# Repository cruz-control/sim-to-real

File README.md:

# Sim-to-real Team

Notes: (4/17/24) 

Solutions:
Got Jetson.GPIO to import by copying into the code directory
Got voltage out on controll pin (jetson servo PWM test)

Issues:
Get Jetson.GPIO to import from default download
Get the servo to run

Links:

Gave us test code
https://forums.developer.nvidia.com/t/strange-behaviour-with-jetson-nano-devkit-pwm-signal/113004/2

Gave us secondary test code
https://stackoverflow.com/questions/69114674/enabling-and-working-with-jetson-gpio-pins-with-python

Possible solution to Jetson.GPIO importing into python
https://forums.developer.nvidia.com/t/jetson-gpio-is-installed-but-cannot-be-imported/264719

Other possible help for identifying PWM and using PWM
https://kernel.org/doc/Documentation/pwm.txt

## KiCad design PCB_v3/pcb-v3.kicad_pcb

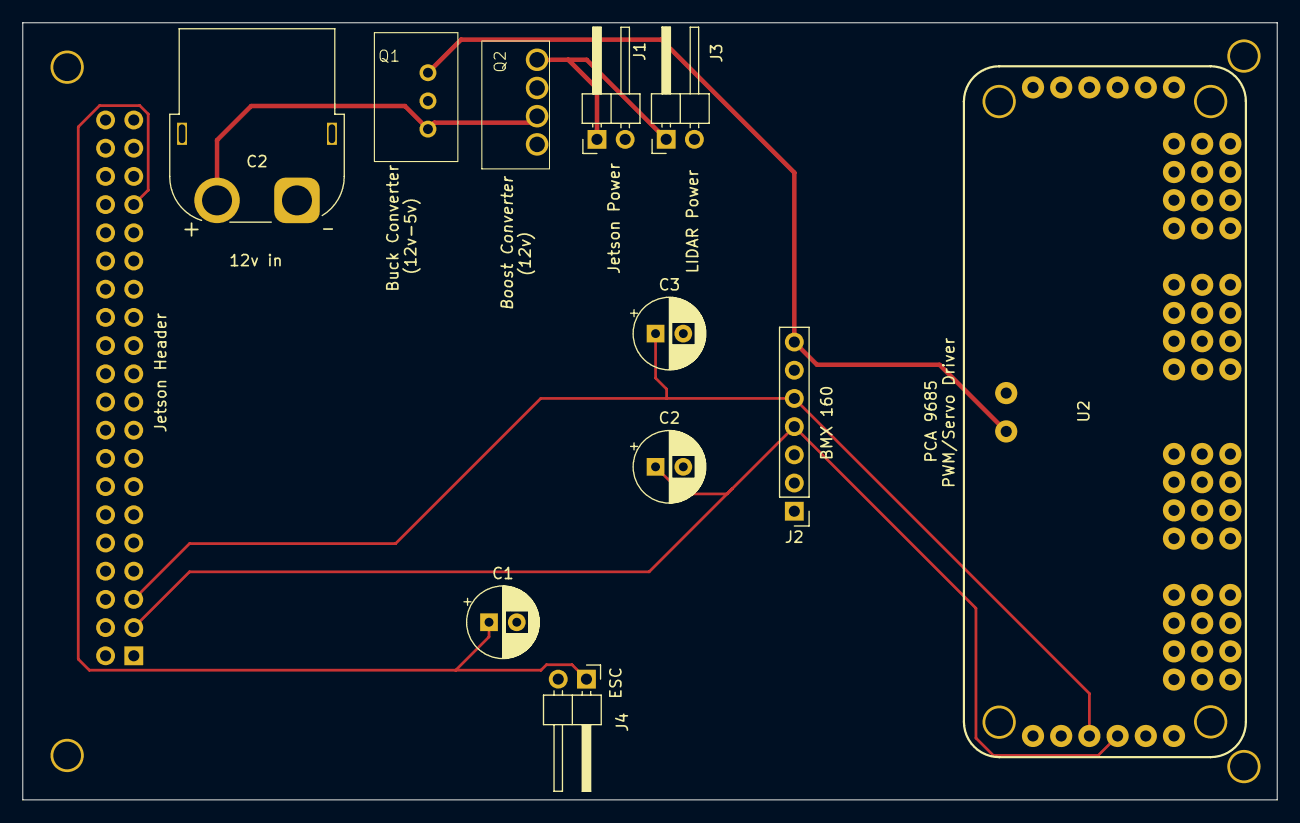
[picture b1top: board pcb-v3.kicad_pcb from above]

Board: 2 copper layers, 113.0 x 70.0 mm, 12 parts (1 on the bottom side), 7 nets.

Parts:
C1, C2, C3: CP_Radial_D6.3mm_P2.50mm
C2#2: AMASS_XT60PW-F_1x02_P7.20mm_Horizontal
J1, J3, J4: Screw_Terminal_01x02; PinHeader_1x02_P2.54mm_Horizontal
J2: Conn_01x07_Socket; PinHeader_1x07_P2.54mm_Vertical
J5: Conn_02x20_Odd_Even; PinSocket_2x20_P2.54mm_Vertical
Q1: LC78_05-3.0
Q2: CRE1S Boost Converter
U2: Adafruit PCA9685 rev C (1)

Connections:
+5V: J2.7, Q1.3 (Vout), U2.24 (A5)
+12V: C2#2.2 (Vout), Q1.1 (Vin), Q2.2 (+Vin)
ESC: C1.1, J4.1, J5.33
GND: C1.2, C2.2, C2#2.1 (Vin), C3.2, J1.2, J2.3, J2.6, J3.2, J4.2, J5.6, J5.9, J5.14, J5.20, J5.25, J5.30, J5.34, J5.39, Q1.2 (GND), Q2.1 (-Vin), Q2.3 (-Vout), U2.14 (GND), U2.25 (EXTCLK)
SCL: C3.1, J2.5, J5.5, U2.4 (A3)
SDA: C2.1, J2.4, J5.3, U2.3 (A2)
STABLE_12V: J1.1, J3.1, Q2.4 (+Vout)

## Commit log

2024-04-13 Jetson updates
2024-04-18 PWM tests
2024-04-19 Cooked
2024-05-06 Updated PCB to V3
2024-05-13 completed board with labels included
2024-05-23 updated PCB
2024-05-24 added mounting holes to PCB
2024-05-24 one more commit lol, forgot one file
2024-05-24 backup
2024-05-24 Updated Files
2024-05-28 Finishing touches
2024-05-28 forgot the Gerb files lol
2024-10-16 Collect LIDAR data in CSV file
2024-11-09 Collect event camera events in DAT files
2024-11-09 Controller Test
